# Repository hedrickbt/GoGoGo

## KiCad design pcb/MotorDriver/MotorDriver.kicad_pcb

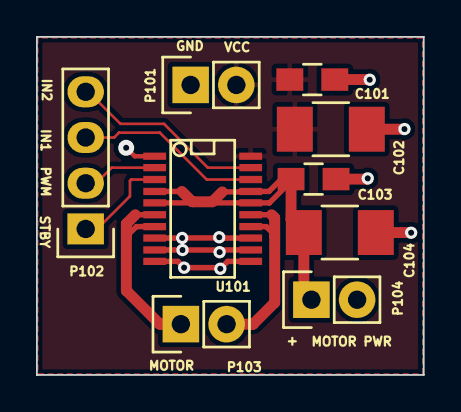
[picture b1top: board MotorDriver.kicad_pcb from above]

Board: 2 copper layers, 21.5 x 18.8 mm, 9 parts (0 on the bottom side), 9 nets.

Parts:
C101, C103: 0.1uf; C_0805_HandSoldering
C102, C104: 10uf; C_1210_HandSoldering
P101, P103, P104: CONN_01X02; Pin_Header_Straight_1x02
P102: CONN_01X04; Pin_Header_Straight_1x04
U101: TB6593FNG; SSOP-20

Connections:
/IN1: P102.3, U101.18
/IN2: P102.4, U101.19
/M+: P103.1, U101.6, U101.7
/PM+: C103.1, C104.1, P104.1, U101.4, U101.5, U101.16, U101.17
/PWM: P102.2, U101.2
/STBY: P102.1, U101.3
GND: C101.2, C102.2, C103.2, C104.2, P101.1, P104.2, U101.1, U101.8, U101.9, U101.10, U101.11, U101.12, U101.13
unnamed: C101.1, C102.1, P101.2, U101.20
unnamed: P103.2, U101.14, U101.15

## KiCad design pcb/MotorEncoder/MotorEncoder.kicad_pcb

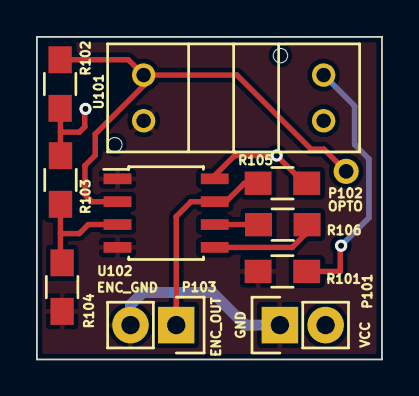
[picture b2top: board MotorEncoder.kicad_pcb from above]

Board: 2 copper layers, 19.2 x 17.9 mm, 11 parts (0 on the bottom side), 8 nets.

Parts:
P101, P103: CONN_01X02; Pin_Header_Straight_1x02
P102: OPTO_OUT; TESTPOINT_1
R101: 100; R_0805_HandSoldering
R102: 10K; R_0805_HandSoldering
R103, R104, R105: 1K; R_0805_HandSoldering
R106: 0; R_0805_HandSoldering
U101: RPI-579N1
U102: LM311DR; SOIC-8_3.9x4.9mm_Pitch1.27mm

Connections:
/ENC_OUT: P103.1, R105.2, U102.7
/OPTO_OUT: P102.1, R102.2, U101.3, U102.2
GND: P101.1, P103.2, R101.2, R104.2, U101.4, U102.1, U102.4
unnamed: R101.1, U101.2
unnamed: R103.2, R104.1, U102.3
unnamed: R106.1, U102.6
unnamed: R106.2, U102.5
VCC: P101.2, R102.1, R103.1, R105.1, U101.1, U102.8

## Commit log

2016-05-24 Just starting stm32 motor test
2016-05-25 Adding first motor test code
2016-05-25 motor test video 2
2016-05-25 motor test video 3 half way done
2016-05-25 motor test code vid 3 finish
2016-05-26 motor test code vid 4
2016-05-30 created stencils for the Encoder and Driver
2016-05-31 working pwm but need to get the velocity changing part to work.
2016-06-01 test now has working driver and encoder
2016-06-01 added docs/pwm_examples
2016-06-26 Removed references to PA_3 for the standby pin as it would not go high.
2016-07-03 Adding the right wheel to the GoGoGo test project.
2016-12-17 Updating ports and pins to match Eric as well as support two motors and a start/stop button
2016-12-19 Got code working with Eric's changes. Added button to start/stop. Refactored wheel code out of main.c
2016-12-19 added pins_connections.txt
2016-12-20 RWI48 setup Ceedling for the stm32/MotorTest1
2016-12-20 RWI49 more Ceedling tests
2016-12-23 Added several unit tests for MotorTest1. The last test remains broken.
2016-12-27 RWI52
2016-12-27 RWI53
2016-12-28 RWI54
2017-01-07 RWI55
2017-01-07 RWI56
2017-01-18 added my first MotorTest1 stm32 project that has been converted to CrossWorks

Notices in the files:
pcb/MotorDriver/MotorDriver.kicad_pcb:
License: CCBY
